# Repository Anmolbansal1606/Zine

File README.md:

# Zine

The first Project consist of controlling Servo Motor from potentiometer.I have upload screenshot and link of Tinkercad.The link for tinkercad stimulation  is https://www.tinkercad.com/things/lK16Lt6TwId?sharecode=M6xJkwNNcQ1MRn0dgx95Y9RonPUCmS-RDPvyrFJcyNM  

The first part of Second project Consist of Controlling Led density with Pwm and made a PCB . I have upload a Code , and both pcb and schmetic file for same.
The tinkercad link for stimulation  is https://www.tinkercad.com/things/dfspQ1BFO2x?sharecode=ttlobSjwfDIhobxnjCzDSXSJt8b9974QFuhftI-3bzE

The second part consist of controlling Servo motor using IR remote without using servo library.i have upload code, The tinkercad link for stimulation is
https://www.tinkercad.com/things/2il6PwhOjFc?sharecode=6upN5bn89mCiGVyqmjdjfmqHzBo09Hh2pk0cZD5_UDQ

The third part consist of making a PCB using kicad containing an Arduino Nano, IR receiver, Buck converter. I have upload a pcb and schmetic file for same.

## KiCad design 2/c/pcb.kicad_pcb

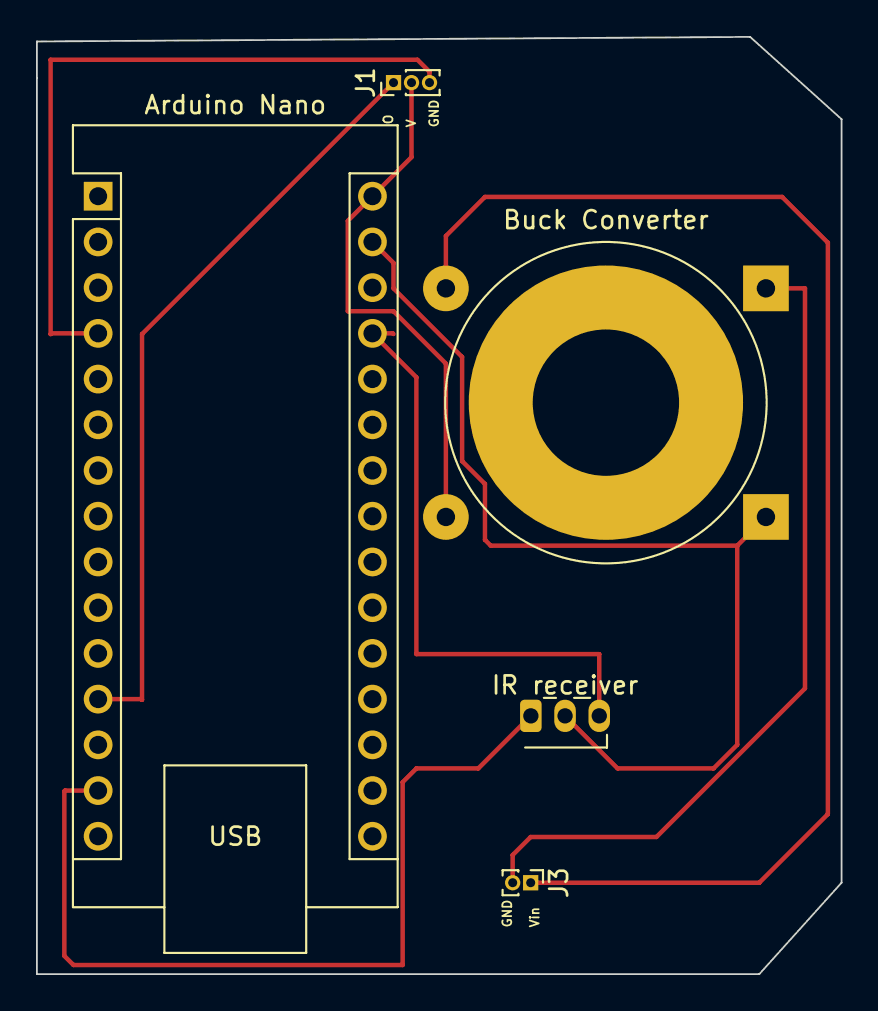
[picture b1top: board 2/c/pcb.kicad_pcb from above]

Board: 2 copper layers, 44.7 x 52.1 mm, 5 parts (0 on the bottom side), 8 nets.

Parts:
Arduino Nano: Arduino_Nano_v2.x; Arduino_Nano
Buck Converter: LM2596S-12; Transformer_Toroid_Horizontal_D18.0mm
IR receiver: TSDP341xx; ONSemi_QSE15x
J1: Conn_01x03_Pin; PinHeader_1x03_P1.00mm_Vertical
J3: Conn_01x02_Pin; PinHeader_1x02_P1.00mm_Vertical

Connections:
unnamed: Arduino Nano.27 (+5V), IR receiver.3 (Vs)
unnamed: Arduino Nano.12 (D9), J1.1
unnamed: Arduino Nano.14 (D11), IR receiver.1 (OUT)
unnamed: Arduino Nano.30 (VIN), Buck Converter.2 (OUT), J1.2
unnamed: Arduino Nano.4 (GND), J1.3
unnamed: Buck Converter.1 (VIN), J3.1
unnamed: Buck Converter.3 (GND), J3.2
unnamed: Arduino Nano.29 (GND), Buck Converter.4 (FB), IR receiver.2 (GND)

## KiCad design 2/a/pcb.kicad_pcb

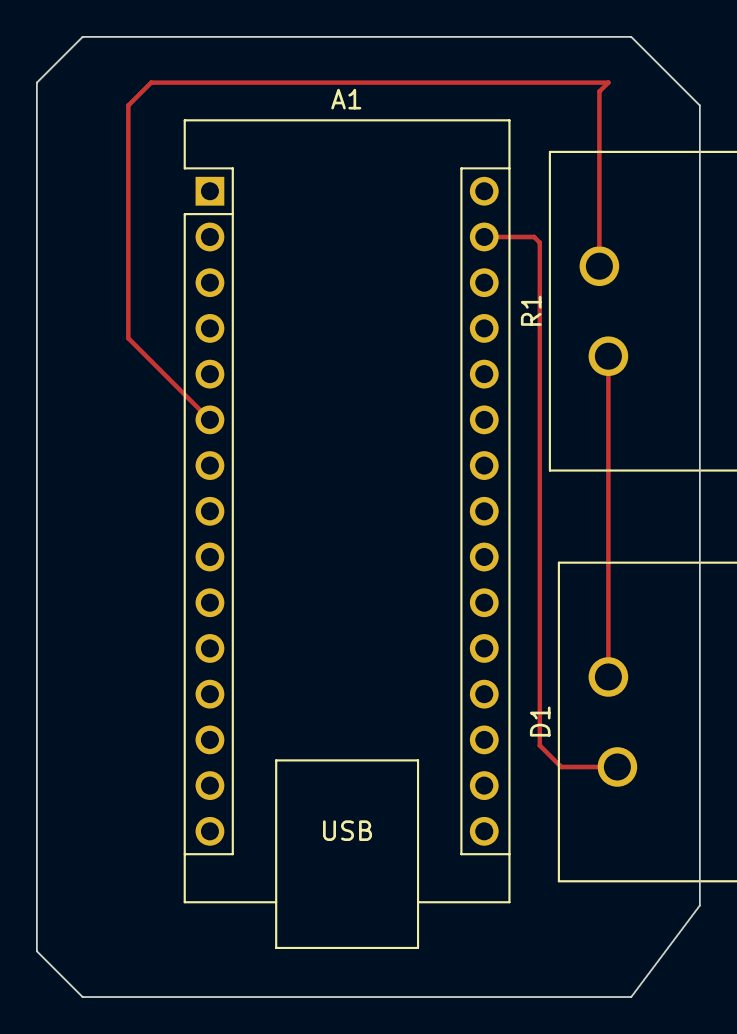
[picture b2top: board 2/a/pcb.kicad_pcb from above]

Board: 2 copper layers, 36.8 x 53.3 mm, 3 parts (0 on the bottom side), 3 nets.

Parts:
A1: Arduino_Nano_v2.x; Arduino_Nano
D1: SW_Push; SW_Matias_1.25u
R1: SW_Push; SW_Matias_1.25u

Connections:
unnamed: A1.6 (D3), R1.1
unnamed: A1.29 (GND), D1.2
unnamed: D1.1, R1.2

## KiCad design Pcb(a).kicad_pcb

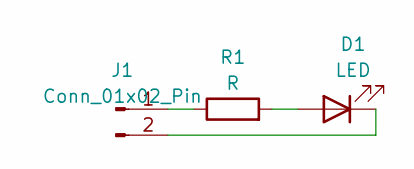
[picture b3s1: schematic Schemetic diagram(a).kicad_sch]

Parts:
D1: LED; LED_D3.0mm
J1: Conn_01x02_Pin; PinHeader_1x02_P1.00mm_Vertical
R1: R; R_Axial_DIN0204_L3.6mm_D1.6mm_P5.08mm_Horizontal

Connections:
unnamed: D1.2 (A), R1.2
unnamed: D1.1 (K), J1.2
unnamed: J1.1, R1.1

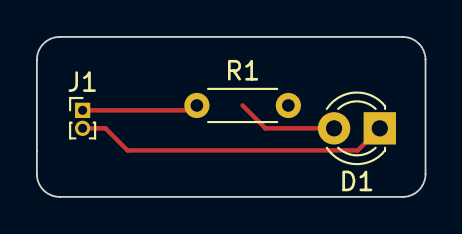
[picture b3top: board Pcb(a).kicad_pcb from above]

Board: 2 copper layers, 21.6 x 8.9 mm, 3 parts (0 on the bottom side), 3 nets.

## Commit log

2023-02-20 This is the part one of second project
2023-02-20 Create 2(a)
2023-02-20 Create a
2023-02-20 Create code
2023-02-22 Rename sketch_feb23b.ino to b
2023-02-23 Create c
2023-02-23 Create d
2023-02-23 Link of Tinkercad is https://www.tinkercad.com/things/lK16Lt6TwId?sharecode=M6xJkwNNcQ1MRn0dgx95Y9RonPUCmS-RDPvyrFJcyNM
2023-02-23 The link for tinkercad stimulation is https://www.tinkercad.com/things/lK16Lt6TwId?sharecode=M6xJkwNNcQ1MRn0dgx95Y9RonPUCmS-RDPvyrFJcyNM
